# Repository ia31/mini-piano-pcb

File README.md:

# Mini Piano: 555 Timer PCB

A five-key electronic piano designed in KiCad for Rice University's ELEC 240.
An LMC555 runs in astable mode, and each key selects a different timing
resistance, setting the frequency of the square wave that drives a piezo buzzer.

[View the schematic (PDF)](PCB%20Design.pdf)

[Front copper (PDF)](PCB%20Design-F_Cu.pdf) · [Back copper (PDF)](PCB%20Design-B_Cu.pdf) · [Board outline (PDF)](PCB%20Design-Edge_Cuts.pdf)

Instead of giving each key its own resistor, R2 through R6 form a single series
ladder, and each key taps a different point on it. Each note's R_B is the
running sum of the resistors above its tap:

| Note | Key | R_B | Theoretical f | Target |
|---|---|---|---|---|
| A5 | SW1 | 5.6k | 907 Hz | 880 Hz |
| G5 | SW2 | 6.6k | 806 Hz | 784 Hz |
| E5 | SW3 | 8.4k | 671 Hz | 659 Hz |
| D5 | SW4 | 9.6k | 604 Hz | 587 Hz |
| C5 | SW5 | 11.1k | 536 Hz | 523 Hz |

With f = 1 / (ln2 * (R_A + 2R_B) * C), R_A = 4.7k, and C = 100 nF.

What this buys:
- **Five standard resistor values make five notes.** No odd values or trimmers.
- **High-note priority for free.** If two keys are pressed, the tap closest to
  the 555 shorts out the ladder below it, so the higher note wins, like a
  monophonic synth.
- **A pentatonic scale.** C, D, E, G, A is the C major pentatonic, so there is
  no wrong note.

## Other details
- 1N5817 Schottky diode for reverse-polarity protection, with lower drop than a
  standard silicon diode
- 10 uF bulk and 100 nF decoupling capacitors, plus 10 nF on the 555 control pin
- Power LED, screw terminal input, and a 1k series resistor on the buzzer
- Two-layer board with ground pours on both layers and zero vias. Through-hole
  pads handle every layer change.
- Keys and ladder resistors are laid out in pitch order, like a keyboard.

## Tuning notes and next revision
Every note comes out 30 to 53 cents sharp in theory. Because the error is
roughly uniform, the whole scale can be pulled down together with one part
change: adding about 2.2 nF in parallel with C1 lowers every note by roughly
the same amount.

## Status
The design is complete. I'm soldering and testing the board this semester, and
I'll add photos and measured frequencies once it's built.

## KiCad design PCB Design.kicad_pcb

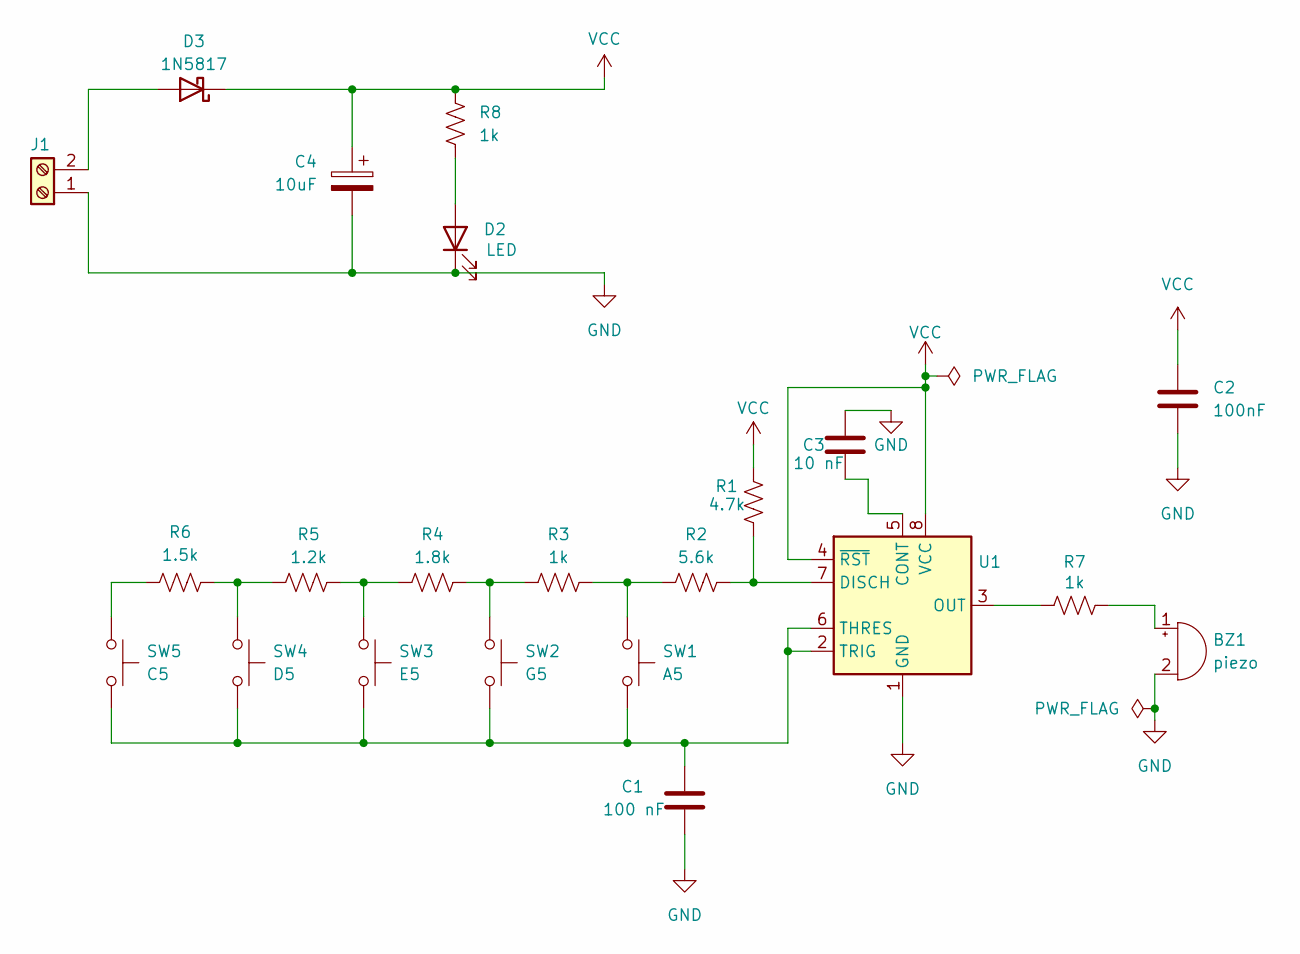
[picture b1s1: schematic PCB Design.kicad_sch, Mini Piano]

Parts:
BZ1: piezo; Buzzer_TDK_PS1240P02BT_D12.2mm_H6.5mm
C1: 100 nF; C_Disc_D5.0mm_W2.5mm_P2.50mm
C2: 100nF; C_Disc_D5.0mm_W2.5mm_P2.50mm
C3: 10 nF; C_Disc_D5.0mm_W2.5mm_P2.50mm
C4: 10uF; CP_Radial_D5.0mm_P2.00mm
D2: LED; LED_D5.0mm
D3: 1N5817; D_DO-41_SOD81_P10.16mm_Horizontal
J1: Screw_Terminal_01x02; TerminalBlock_Phoenix_MKDS-1,5-2-5.08_1x02_P5.08mm_Horizont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
R1: 4.7k; R_Axial_DIN0207_L6.3mm_D2.5mm_P10.16mm_Horizontal
R2: 5.6k; R_Axial_DIN0207_L6.3mm_D2.5mm_P10.16mm_Horizontal
R3, R7, R8: 1k; R_Axial_DIN0207_L6.3mm_D2.5mm_P10.16mm_Horizontal
R4: 1.8k; R_Axial_DIN0207_L6.3mm_D2.5mm_P10.16mm_Horizontal
R5: 1.2k; R_Axial_DIN0207_L6.3mm_D2.5mm_P10.16mm_Horizontal
R6: 1.5k; R_Axial_DIN0207_L6.3mm_D2.5mm_P10.16mm_Horizontal
SW1: A5; SW_PUSH_6mm
SW2: G5; SW_PUSH_6mm
SW3: E5; SW_PUSH_6mm
SW4: D5; SW_PUSH_6mm
SW5: C5; SW_PUSH_6mm
U1: LMC555xN; DIP-8_W7.62mm

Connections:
GND: BZ1.2 (-), C1.2, C2.2, C3.1, C4.2, D2.1 (K), J1.1, U1.1 (GND)
unnamed: BZ1.1 (+), R7.2
unnamed: D2.2 (A), R8.2
unnamed: D3.2 (A), J1.2
unnamed: R2.1, R3.2, SW1.1
unnamed: R3.1, R4.2, SW2.1
unnamed: R4.1, R5.2, SW3.1
unnamed: R5.1, R6.2, SW4.1
unnamed: R6.1, SW5.1
unnamed: C3.2, U1.5 (CONT)
unnamed: R1.2, R2.2, U1.7 (DISCH)
unnamed: R7.1, U1.3 (OUT)
unnamed: C1.1, SW1.2, SW2.2, SW3.2, SW4.2, SW5.2, U1.2 (TRIG), U1.6 (THRES)
VCC: C2.1, C4.1, D3.1 (K), R1.1, R8.1, U1.4 (~RST), U1.8 (VCC)

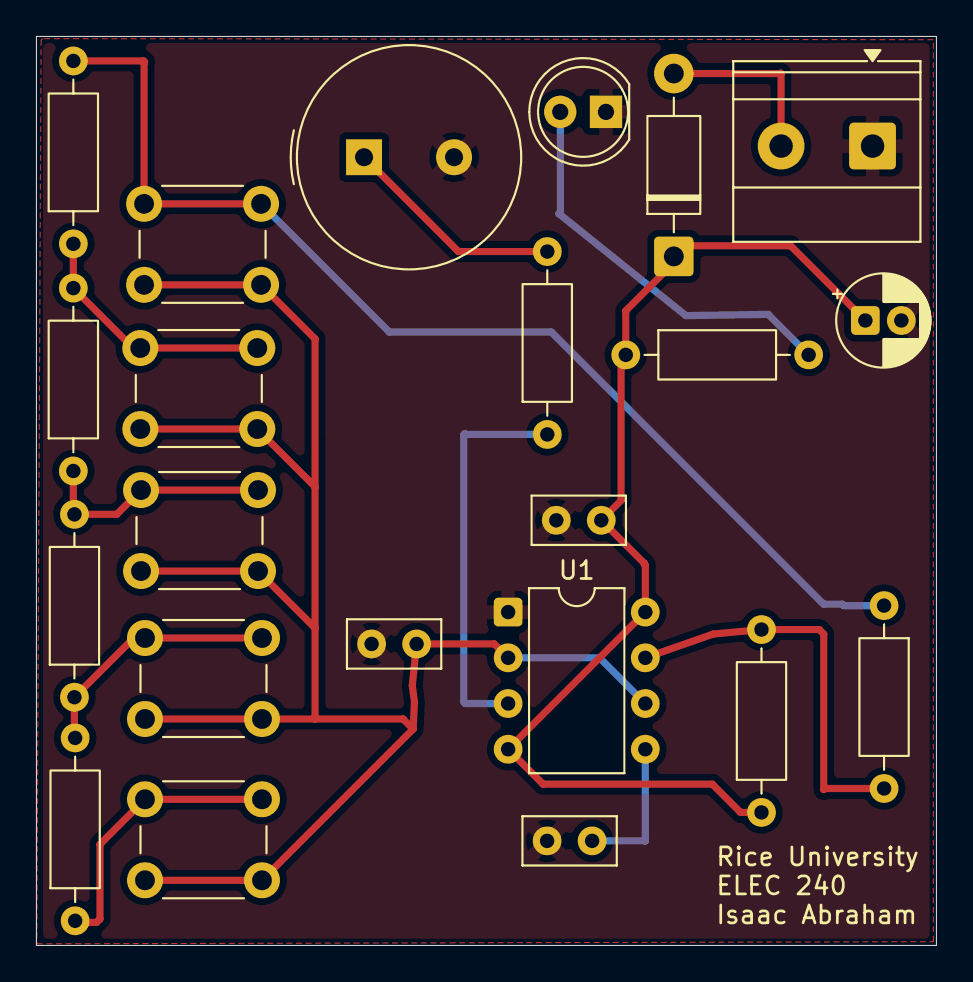
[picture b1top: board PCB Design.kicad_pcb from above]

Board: 2 copper layers, 50.0 x 50.5 mm, 22 parts (0 on the bottom side), 14 nets.
